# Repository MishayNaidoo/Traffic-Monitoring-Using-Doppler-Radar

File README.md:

# Traffic-Monitoring-Using-Doppler-Radar

This repository details an investigation conducted by Mishay Naidoo for his EEE4022S Final year engineering project. The aim of the project was to design a traffic monitoring system using a low-cost Doppler radar. 
This project was done under the supervision of Prof. Amit Mishra of the University of Cape Town.

There is a pdf of the report describing the entire project in detail.
The code used in the report is located in the Algorithms folder.
The images generated using code are located in the ReportPlots folder. 
The extras folder just includes all of the files used when working on this project. All of the important files are in the other two folders.

# Contact Me

Feel free to contact me at: naidoo.mishay@gmail.com

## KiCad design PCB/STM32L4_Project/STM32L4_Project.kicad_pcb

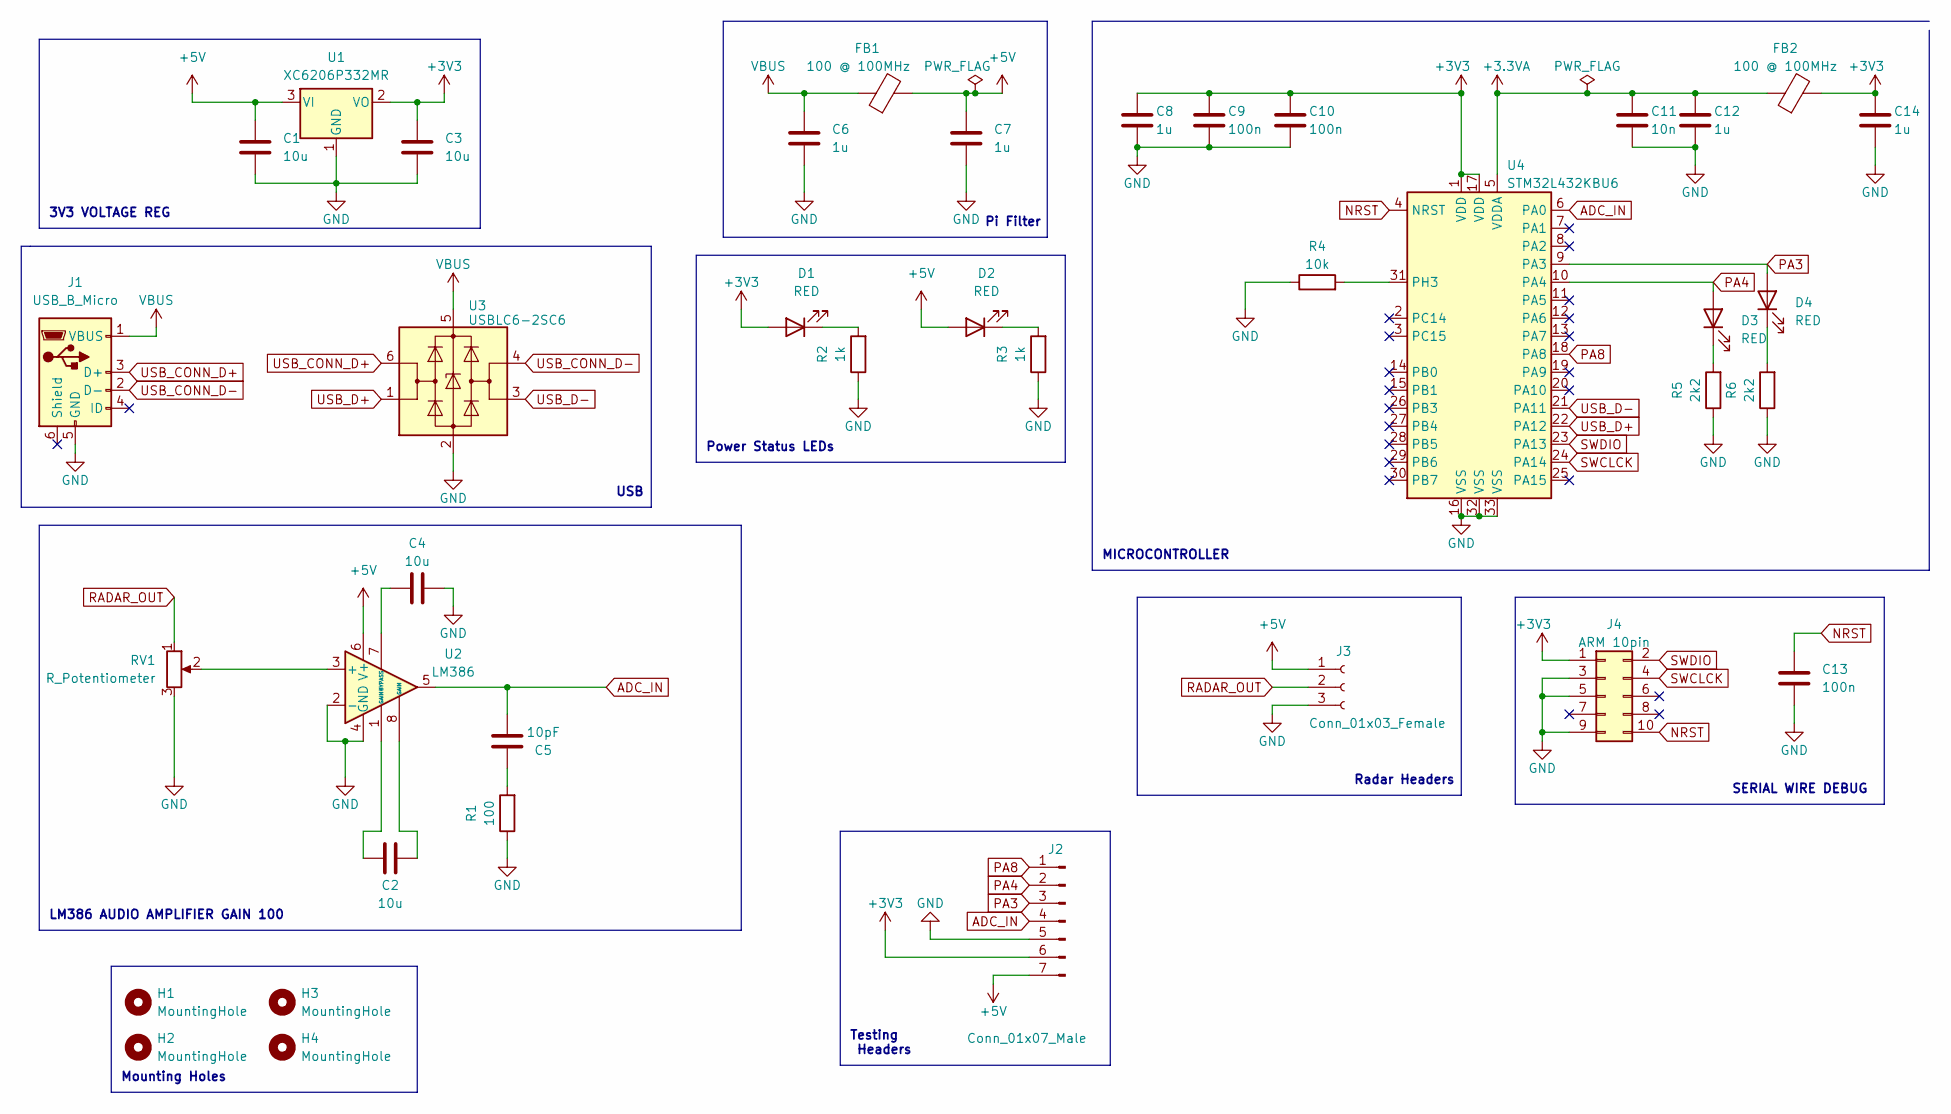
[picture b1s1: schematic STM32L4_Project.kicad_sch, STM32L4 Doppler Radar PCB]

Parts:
C1, C2, C3, C4: 10u; C_0603_1608Metric
C5: 10pF; C_0402_1005Metric
C6, C7, C8, C12, C14: 1u; C_0603_1608Metric
C9, C10, C13: 100n; C_0402_1005Metric
C11: 10n; C_0402_1005Metric
D1, D2, D3, D4: RED; LED_0603_1608Metric
FB1, FB2: 100 @ 100MHz; L_0805_2012Metric
H1, H2, H3, H4: MountingHole; MountingHole_2.2mm_M2
J1: USB_B_Micro; USB_Micro-B_Molex_47346-0001
J2: Conn_01x07_Male; PinHeader_1x07_P2.54mm_Vertical
J3: Conn_01x03_Female; PinSocket_1x03_P2.54mm_Vertical
J4: ARM 10pin; PinHeader_2x05_P2.54mm_Vertical
R1: 100; R_0402_1005Metric
R2, R3: 1k; R_0402_1005Metric
R4: 10k; R_0402_1005Metric
R5, R6: 2k2; R_0402_1005Metric
RV1: R_Potentiometer; Potentiometer_Bourns_3296W_Vertical
U1: XC6206P332MR; SOT-23
U2: LM386; SOIC-8_3.9x4.9mm_P1.27mm
U3: USBLC6-2SC6; SOT-23-6
U4: STM32L432KBU6; QFN-32-1EP_5x5mm_P0.5mm_EP3.45x3.45mm

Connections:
+3.3VA: C11.1, C12.1, FB2.1, U4.5 (VDDA)
+3V3: C3.1, C8.1, C9.1, C10.1, C14.1, D1.2 (A), FB2.2, J2.6, J4.1, U1.2 (VO), U4.1 (VDD), U4.17 (VDD)
+5V: C1.1, C7.1, D2.2 (A), FB1.2, J2.7, J3.1, U1.3 (VI), U2.6 (V+)
ADC_IN: C5.2, J2.4, U2.5, U4.6 (PA0)
GND: C1.2, C3.2, C4.2, C6.2, C7.2, C8.2, C9.2, C10.2, C11.2, C12.2, C13.2, C14.2, J1.5 (GND), J2.5, J3.3, J4.3, J4.5, J4.9, R1.1, R2.1, R3.1, R4.1, R5.1, R6.1, RV1.3, U1.1 (GND), U2.2 (-), U2.4 (GND), U3.2 (GND), U4.16 (VSS), U4.32 (VSS), U4.33 (VSS)
NRST: C13.1, J4.10, U4.4 (NRST)
unnamed: C2.1, U2.1 (GAIN)
unnamed: C2.2, U2.8 (GAIN)
unnamed: C4.1, U2.7 (BYPASS)
unnamed: C5.1, R1.2
unnamed: D1.1 (K), R2.2
unnamed: D2.1 (K), R3.2
unnamed: D3.1 (K), R5.2
unnamed: D4.1 (K), R6.2
unnamed: R4.2, U4.31 (PH3)
unnamed: RV1.2, U2.3 (+)
PA3: D4.2 (A), J2.3, U4.9 (PA3)
PA4: D3.2 (A), J2.2, U4.10 (PA4)
PA8: J2.1, U4.18 (PA8)
RADAR_OUT: J3.2, RV1.1
SWCLCK: J4.4, U4.24 (PA14)
SWDIO: J4.2, U4.23 (PA13)
USB_CONN_D+: J1.3 (D+), U3.6 (I/O1)
USB_CONN_D-: J1.2 (D-), U3.4 (I/O2)
USB_D+: U3.1 (I/O1), U4.22 (PA12)
USB_D-: U3.3 (I/O2), U4.21 (PA11)
VBUS: C6.1, FB1.1, J1.1 (VBUS), U3.5 (VBUS)

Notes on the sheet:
LM386 AUDIO AMPLIFIER GAIN 100
USB
Power Status LEDs
Testing Headers
SERIAL WIRE DEBUG
MICROCONTROLLER
Pi Filter
3V3 VOLTAGE REG
Mounting Holes
Radar Headers

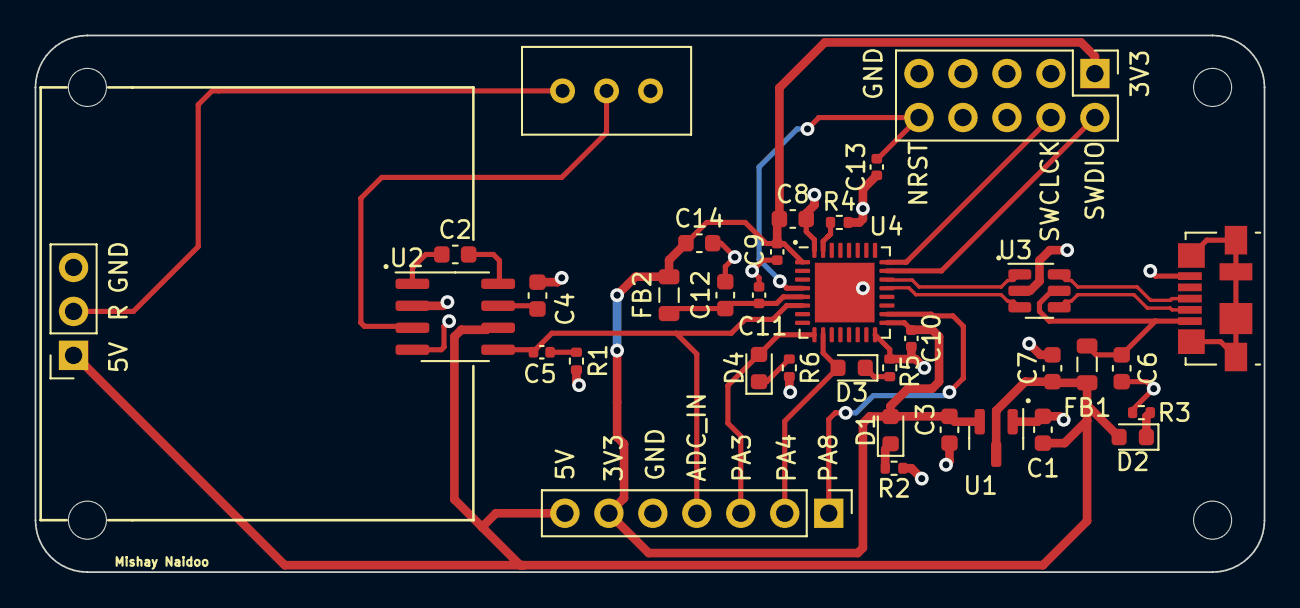
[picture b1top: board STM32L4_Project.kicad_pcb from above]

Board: 2 copper layers, 71.0 x 31.0 mm, 39 parts (0 on the bottom side), 27 nets.

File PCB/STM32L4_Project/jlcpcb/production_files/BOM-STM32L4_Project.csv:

Comment,Designator,Footprint,LCSC
100 @ 100MHz,"FB1,FB2",L_0805_2012Metric,C1015
1k,"R2,R3",R_0402_1005Metric,C11702
USB_B_Micro,J1,USB_Micro-B_Molex_47346-0001,C132560
10n,C11,C_0402_1005Metric,C15195
100n,"C10,C13,C9",C_0402_1005Metric,C1525
1u,"C12,C14,C6,C7,C8",C_0603_1608Metric,C15849
10u,"C1,C2,C3,C4",C_0603_1608Metric,C19702
RED,"D1,D2,D3,D4",LED_0603_1608Metric,C2286
100,R1,R_0402_1005Metric,C25076
10k,R4,R_0402_1005Metric,C25744
2k2,"R5,R6",R_0402_1005Metric,C25879
USBLC6-2SC6,U3,SOT-23-6,C2827654
10pF,C5,C_0402_1005Metric,C32949
R_Potentiometer,RV1,Potentiometer_Bourns_3296W_Vertical,C34846
LM386,U2,SOIC-8_3.9x4.9mm_P1.27mm,C510560
XC6206P332MR,U1,SOT-23,C5446
STM32L432KBU6,U4,QFN-32-1EP_5x5mm_P0.5mm_EP3.45x3.45mm,C94784

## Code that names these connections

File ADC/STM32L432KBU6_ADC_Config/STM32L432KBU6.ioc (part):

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Mcu.Name=STM32L432K(B-C)Ux
Mcu.Package=UFQFPN32
Mcu.UserName=STM32L432KBUx
PA0.Signal=ADCx_IN5
PA11.Mode=Device
PA11.Signal=USB_DM
PA12.Mode=Device
PA12.Signal=USB_DP
PA13\ (JTMS-SWDIO).Mode=Serial_Wire
PA13\ (JTMS-SWDIO).Signal=SYS_JTMS-SWDIO
PA14\ (JTCK-SWCLK).Mode=Serial_Wire
PA14\ (JTCK-SWCLK).Signal=SYS_JTCK-SWCLK
PA3.GPIOParameters=GPIO_Label
PA3.GPIO_Label=LED_Comms
PA3.Signal=GPIO_Output
PA4.GPIOParameters=GPIO_Label
PA4.GPIO_Label=GPIO_ADC
PA4.Signal=GPIO_Output
PA8.Signal=S_TIM1_CH1
RCC.HSE_VALUE=8000000
RCC.SYSCLKFreq_VALUE=80000000
RCC.SYSCLKSource=RCC_SYSCLKSOURCE_PLLCLK
board=custom

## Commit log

2023-08-19 Creating the 4022S Repo
2023-08-21 add BOM and other stuff
2023-09-12 added alot of stuff
2023-09-14 added more data from Firth Road
2023-09-20 Added firth road data
2023-10-03 Everything Bar WestStopTest FinalCDM and PowerSupply
2023-10-05 Update PiScript files to work on pi zero
2023-10-05 testing getting the recording working on pi zero
2023-10-05 still testing pi zero
2023-10-05 Still testing
2023-10-05 still fixing pi zero stuff
2023-10-05 Testing
2023-10-06 added a new continuous py file
2023-10-06 updated the continuous script v2
2023-10-06 increased buffer size
2023-10-11 Added first draft of final code
2023-10-18 added final dataset, removed google drive scripts
2023-10-20 Final Implementation Added
2023-10-28 Final Repo Changes
2023-10-28 Update Theory Plots
2023-10-29 Create LICENSE
2023-10-30 Added Final Report
2024-01-29 Delete Extras/Images/Theory/Spectrogram /.DS_Store
    Deleted DS_Store file in Spectrogram
2024-01-29 Rename HannWindow.pdf to HannWindow.pdf
2024-01-29 Rename SpectrogramMathsFullSignal.png to SpectrogramMathsFullSignal.png
2024-01-29 Rename SpectrogramMathsW1.png to SpectrogramMathsW1.png
2024-01-29 Rename SpectrogramMathsW2.png to SpectrogramMathsW2.png
2024-01-29 Rename SpectrogramMathsW3.png to SpectrogramMathsW3.png
2024-01-29 Rename SpectrogramMathsW4.png to SpectrogramMathsW4.png
2024-01-29 Rename SpectrogramWindowed.jpeg to SpectrogramWindowed.jpeg
2024-01-30 Reorganised for masters work and created a Target_ID_4022 folder
2024-01-30 Tested git login
2024-01-30 Still testing login stuff
2024-01-30 Testing login stuff some more
2024-01-31 Please dont be Daniel
2024-02-08 Added files interfacing with the MCP3914 with various micros as well as a Blinky Script using VScode for the STM32
2024-02-19 Added a STM32 MCP9314 File for interfacing with the adc
2024-02-20 Added Drivers for MCP3914
2024-03-12 Added working ADC recording code using STM32F4
2024-03-30 Added PCB design
2024-03-31 More work on PCB
2024-03-31 More PCB Changes
2024-04-08 Added word doc to describe progress
2024-04-24 added some housing stuff and other changes
2024-04-30 Added working PCB script
2024-05-13 Updated Serial Reader scripts to write raw data to output.txt
2024-05-18 Still working on the MCP3914 SPI Code
2024-05-21 Debugging SPI and DMA in the STM32F4_MCP3914_USB
2024-05-21 More work on the STM32F4_MCP3914_USB script. Still not complete.
2024-05-21 Added the DC power supply data from Radar lab to the HumanWalkingData folder
2024-05-24 Updated documentation and added F4 CDM324 human walking data
2024-05-24 Just messing with the human walking plots
2024-05-24 Captured more walking data in radar lab
2024-05-24 Updated the walking data
2024-05-28 Updated the documentation for PCB v2, started schematic for PCB v2
2024-05-29 Added ADA8282 Symbol to KICAD and ADA8282 Datasheet under Amplifiers
2024-06-02 Collected more human walking data in radar lab
2024-06-03 Created the amplifier PCB for the ADA8282
2024-06-05 Worked on PCB V2 and Added Instrumentation Amp test data
2024-06-07 Successfully Captured AD620 Data
2024-06-08 Added some processing to AD620 Walking Data
2024-08-06 Updated File Layout
2024-08-13 Added the Motion_Tests folder with some data with amplifier board and PCM2900
2024-08-15 Added more plots to the motion tests folder
2024-09-01 Added stm32h7 adc scripts
2024-09-01 Improved STM32H7 ADC Data Acquisition
2024-09-23 Added some ADAU1979 AD8422 Walking Data to RadarHumanData Folder
2024-10-07 Added some MCP6024 walking data
2024-10-14 Captured some actual car data stored in radar car data folder
2025-01-18 Test
2025-02-21 Added ADAU1372 Drivers
